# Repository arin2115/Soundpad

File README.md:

# arin's 8-key soundpad project

## Features:
- 8 keys configurable in my software
- 8 rgb leds

## Images
Schematic            |  PCB
:-------------------------:|:-------------------------:
  |  

CAD Model:

I made it in Shapr3D as it is easier for me than Fusion360.

## BOM
- 4x M3x16mm screws
- 4x M3x5mx4mm heatset inserts
- 8x SK6812 MINI-E LEDs
- 1x Seeed XIAO RP2040
- 8x MX-Style switches
- 8x Blank DSA keycaps

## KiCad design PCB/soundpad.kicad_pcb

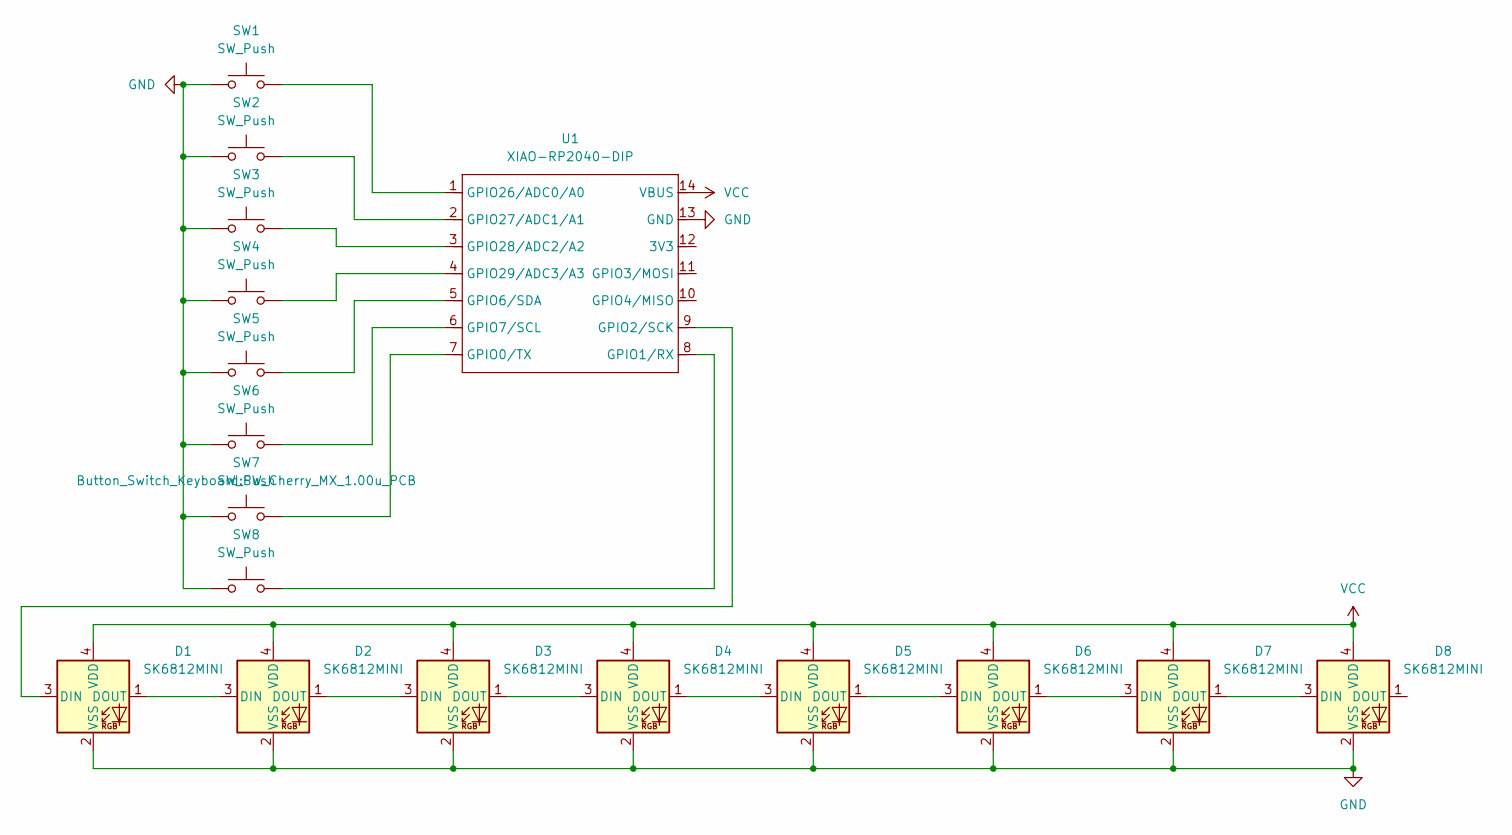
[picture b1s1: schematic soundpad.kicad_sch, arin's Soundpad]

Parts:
D1, D2, D3, D4, D5, D6, D7, D8: SK6812MINI; LED_SK6812MINI_PLCC4_3.5x3.5mm_P1.75mm
SW1, SW2, SW3, SW4, SW5, SW6, SW7, SW8: SW_Push; SW_Cherry_MX_1.00u_PCB
U1: XIAO-RP2040-DIP

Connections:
GND: D1.2 (VSS), D2.2 (VSS), D3.2 (VSS), D4.2 (VSS), D5.2 (VSS), D6.2 (VSS), D7.2 (VSS), D8.2 (VSS), SW1.1, SW2.1, SW3.1, SW4.1, SW5.1, SW6.1, SW7.1, SW8.1, U1.13 (GND)
unnamed: D1.3 (DIN), U1.9 (GPIO2/SCK)
unnamed: D1.1 (DOUT), D2.3 (DIN)
unnamed: D2.1 (DOUT), D3.3 (DIN)
unnamed: D3.1 (DOUT), D4.3 (DIN)
unnamed: D4.1 (DOUT), D5.3 (DIN)
unnamed: D5.1 (DOUT), D6.3 (DIN)
unnamed: D6.1 (DOUT), D7.3 (DIN)
unnamed: D7.1 (DOUT), D8.3 (DIN)
unnamed: SW7.2, U1.7 (GPIO0/TX)
unnamed: SW8.2, U1.8 (GPIO1/RX)
unnamed: SW5.2, U1.5 (GPIO6/SDA)
unnamed: SW6.2, U1.6 (GPIO7/SCL)
unnamed: SW1.2, U1.1 (GPIO26/ADC0/A0)
unnamed: SW2.2, U1.2 (GPIO27/ADC1/A1)
unnamed: SW3.2, U1.3 (GPIO28/ADC2/A2)
unnamed: SW4.2, U1.4 (GPIO29/ADC3/A3)
VCC: D1.4 (VDD), D2.4 (VDD), D3.4 (VDD), D4.4 (VDD), D5.4 (VDD), D6.4 (VDD), D7.4 (VDD), D8.4 (VDD), U1.14 (VBUS)

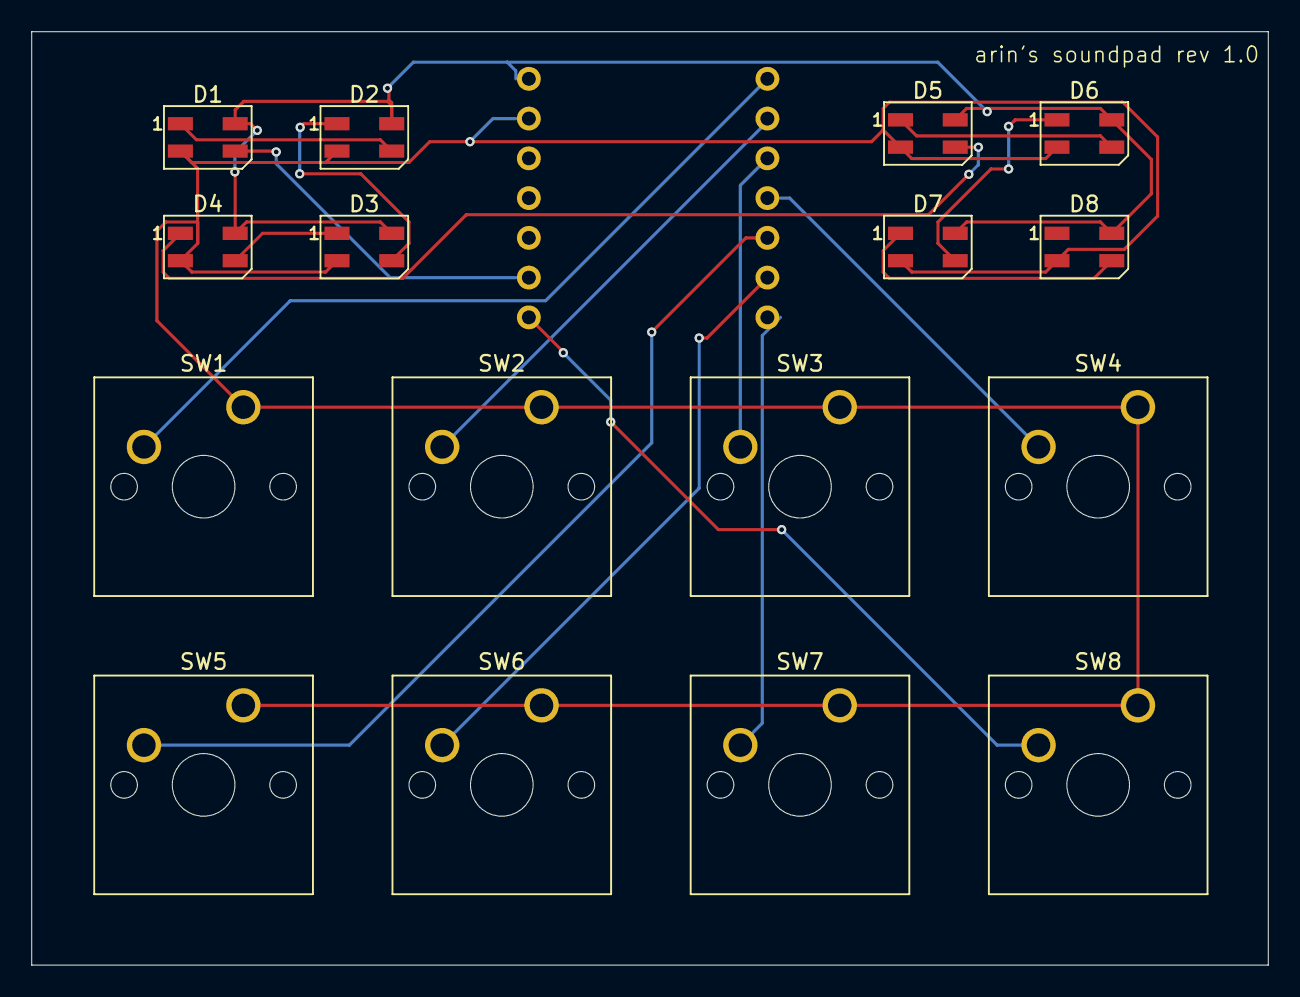
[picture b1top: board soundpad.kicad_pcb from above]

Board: 2 copper layers, 79.0 x 59.6 mm, 17 parts (1 on the bottom side), 18 nets.

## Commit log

2025-12-26 pcb upload
2025-12-26 Revise README for 8-key soundpad project
    Updated project title and added features, images, and BOM.
2025-12-26 Initialize KMKKeyboard with keymap and scanner
